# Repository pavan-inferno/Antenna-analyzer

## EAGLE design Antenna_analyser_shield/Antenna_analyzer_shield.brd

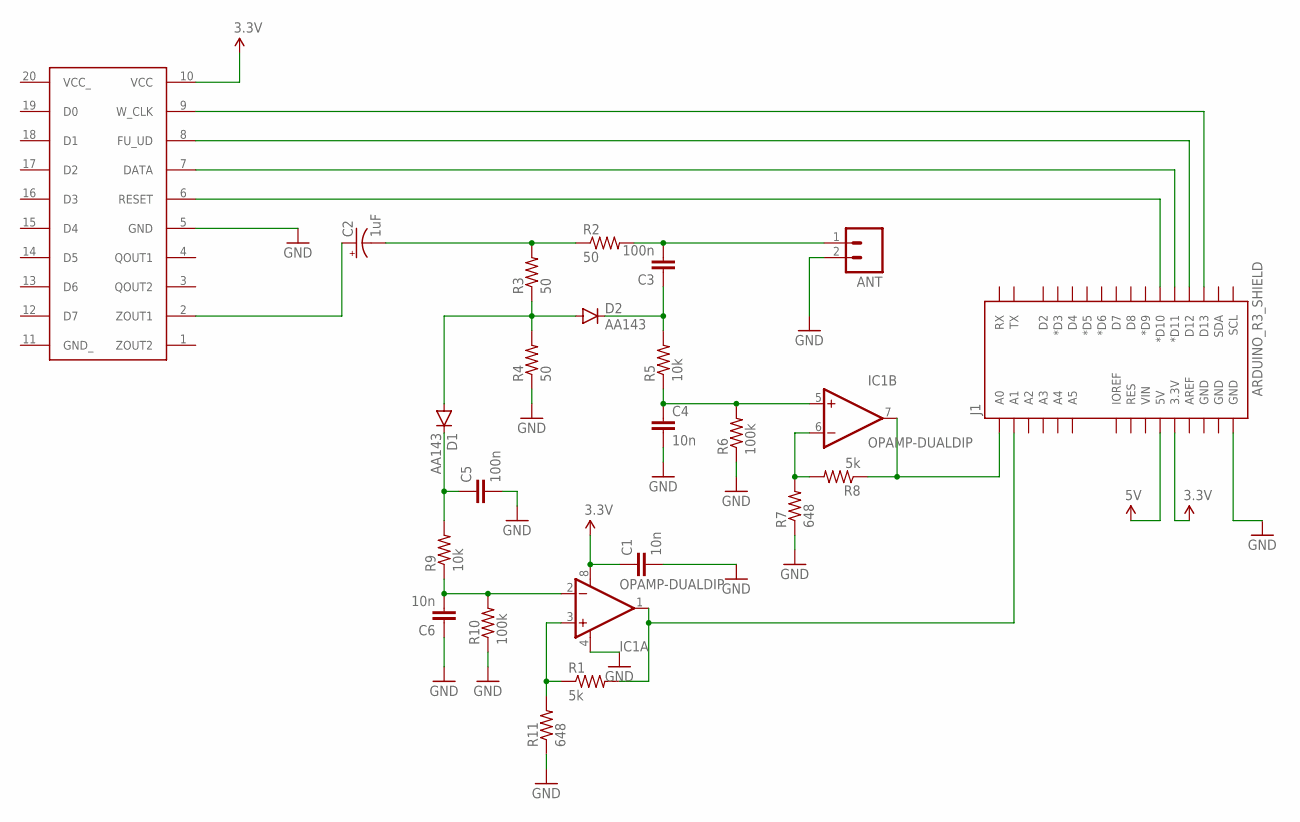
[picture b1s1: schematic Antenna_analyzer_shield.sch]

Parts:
ANT: M023.5MM; SCREWTERMINAL-3.5MM-2
C1, C4, C6: 10n; CAP-PTH-SMALL2
C2: 1uF; CPOL-RADIAL-10UF-25V
C3, C5: 100n; CAP-PTH-SMALL2
D1, D2: AA143; DIODE-1N4001
IC1: OPAMP-DUALDIP; DIP08
J1: ARDUINO_R3_SHIELD; UNO_R3_SHIELD
R1, R8: 5k; AXIAL-0.4
R2, R3, R4: 50; AXIAL-0.4
R5, R9: 10k; AXIAL-0.4
R6, R10: 100k; AXIAL-0.4
R7, R11: 648; AXIAL-0.4
U$1: DDS; 1X10_NO_SILK

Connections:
5V: C1.1, IC1.8 (V+), J1.3.3V, J1.5V, U$1.10 (VCC)
GND: ANT.2, C1.2, C4.2, C5.2, C6.1, IC1.4 (V-), J1.GND@0 (GND), R4.P$1 (1), R6.P$1 (1), R7.P$1 (1), R10.P$1 (1), R11.P$1 (1), U$1.5 (GND)
unnamed: C2.2 (-), R2.P$1 (1), R3.P$2 (2)
unnamed: ANT.1, C3.2, R2.P$2 (2)
unnamed: D1.A, D2.A, R3.P$1 (1), R4.P$2 (2)
unnamed: C3.1, D2.C, R5.P$2 (2)
unnamed: C4.1, IC1.5 (+IN), R5.P$1 (1), R6.P$2 (2)
unnamed: IC1.6 (-IN), R7.P$2 (2), R8.P$2 (2)
unnamed: IC1.7 (OUT), J1.A0, R8.P$1 (1)
unnamed: C6.2, IC1.2 (-IN), R9.P$1 (1), R10.P$2 (2)
unnamed: IC1.3 (+IN), R1.P$1 (1), R11.P$2 (2)
unnamed: IC1.1 (OUT), J1.A1, R1.P$2 (2)
unnamed: C5.1, D1.C, R9.P$2 (2)
unnamed: C2.1 (+), U$1.2 (ZOUT1)
unnamed: J1.D13, U$1.9 (W_CLK)
unnamed: J1.D12, U$1.8 (FU_UD)
unnamed: J1.D11 (*D11), U$1.7 (DATA)
unnamed: J1.D10 (*D10), U$1.6 (RESET)

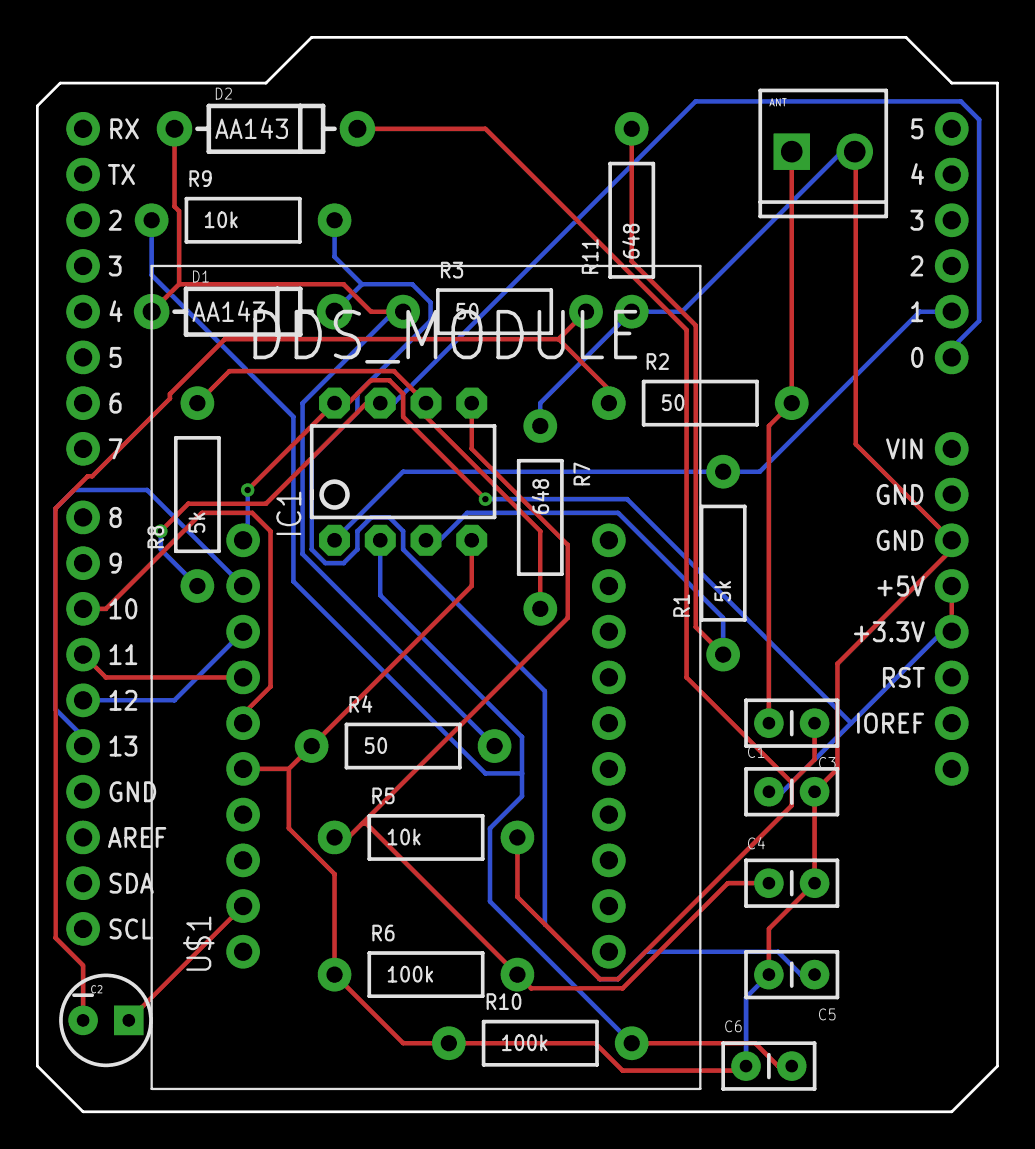
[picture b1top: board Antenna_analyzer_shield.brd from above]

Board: 2 copper layers, 53.3 x 59.7 mm, 23 parts (0 on the bottom side), 18 nets.

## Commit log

2017-09-25 Shield schematics added
2017-09-27 First working code
    Verified that the DDS module is working properly.
    But the VSWR values are way off. This may be due to the substitution of AA143 diode with 1N34A.
2017-09-27 changed the pin for TFT chip select
2017-10-01 Frequency sweeps done
2017-10-02 display minimum feature implemented
2017-10-06 routine stuff
2017-11-02 Calibration added
2017-11-17 plotting implemented

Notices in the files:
parts and their libraries:
SparkFun-Connectors: Licensing: Creative Commons ShareAlike 4.0 International - https://creativecommons.org/licenses/by-sa/4.0
